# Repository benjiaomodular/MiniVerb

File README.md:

# MiniVerb
A reverb module based around the Daisy Seed platform.

## PCB Versions
### 2.1
Finally, a working SMT version

Download zip files from: [Hardware/MiniVerb v2.1/Fabrication](Hardware/MiniVerb%20v2.1/Fabrication)

### 2.0 (not working)
First SMT Release. This version was unusable.
- Added a single CV input

### 1.1
First batch of corrections
- Fixed pot connections
- Make IN(R) use IN(L) when no jack is inserted.

Download zip files from: [Hardware/MiniVerb v1.1/Fabrication](Hardware/MiniVerb%20v1.1/Fabrication)

### 1.0 (not working)
Initial release (does not work out of the box)
- Pots connected to the wrong pins on the Daisy

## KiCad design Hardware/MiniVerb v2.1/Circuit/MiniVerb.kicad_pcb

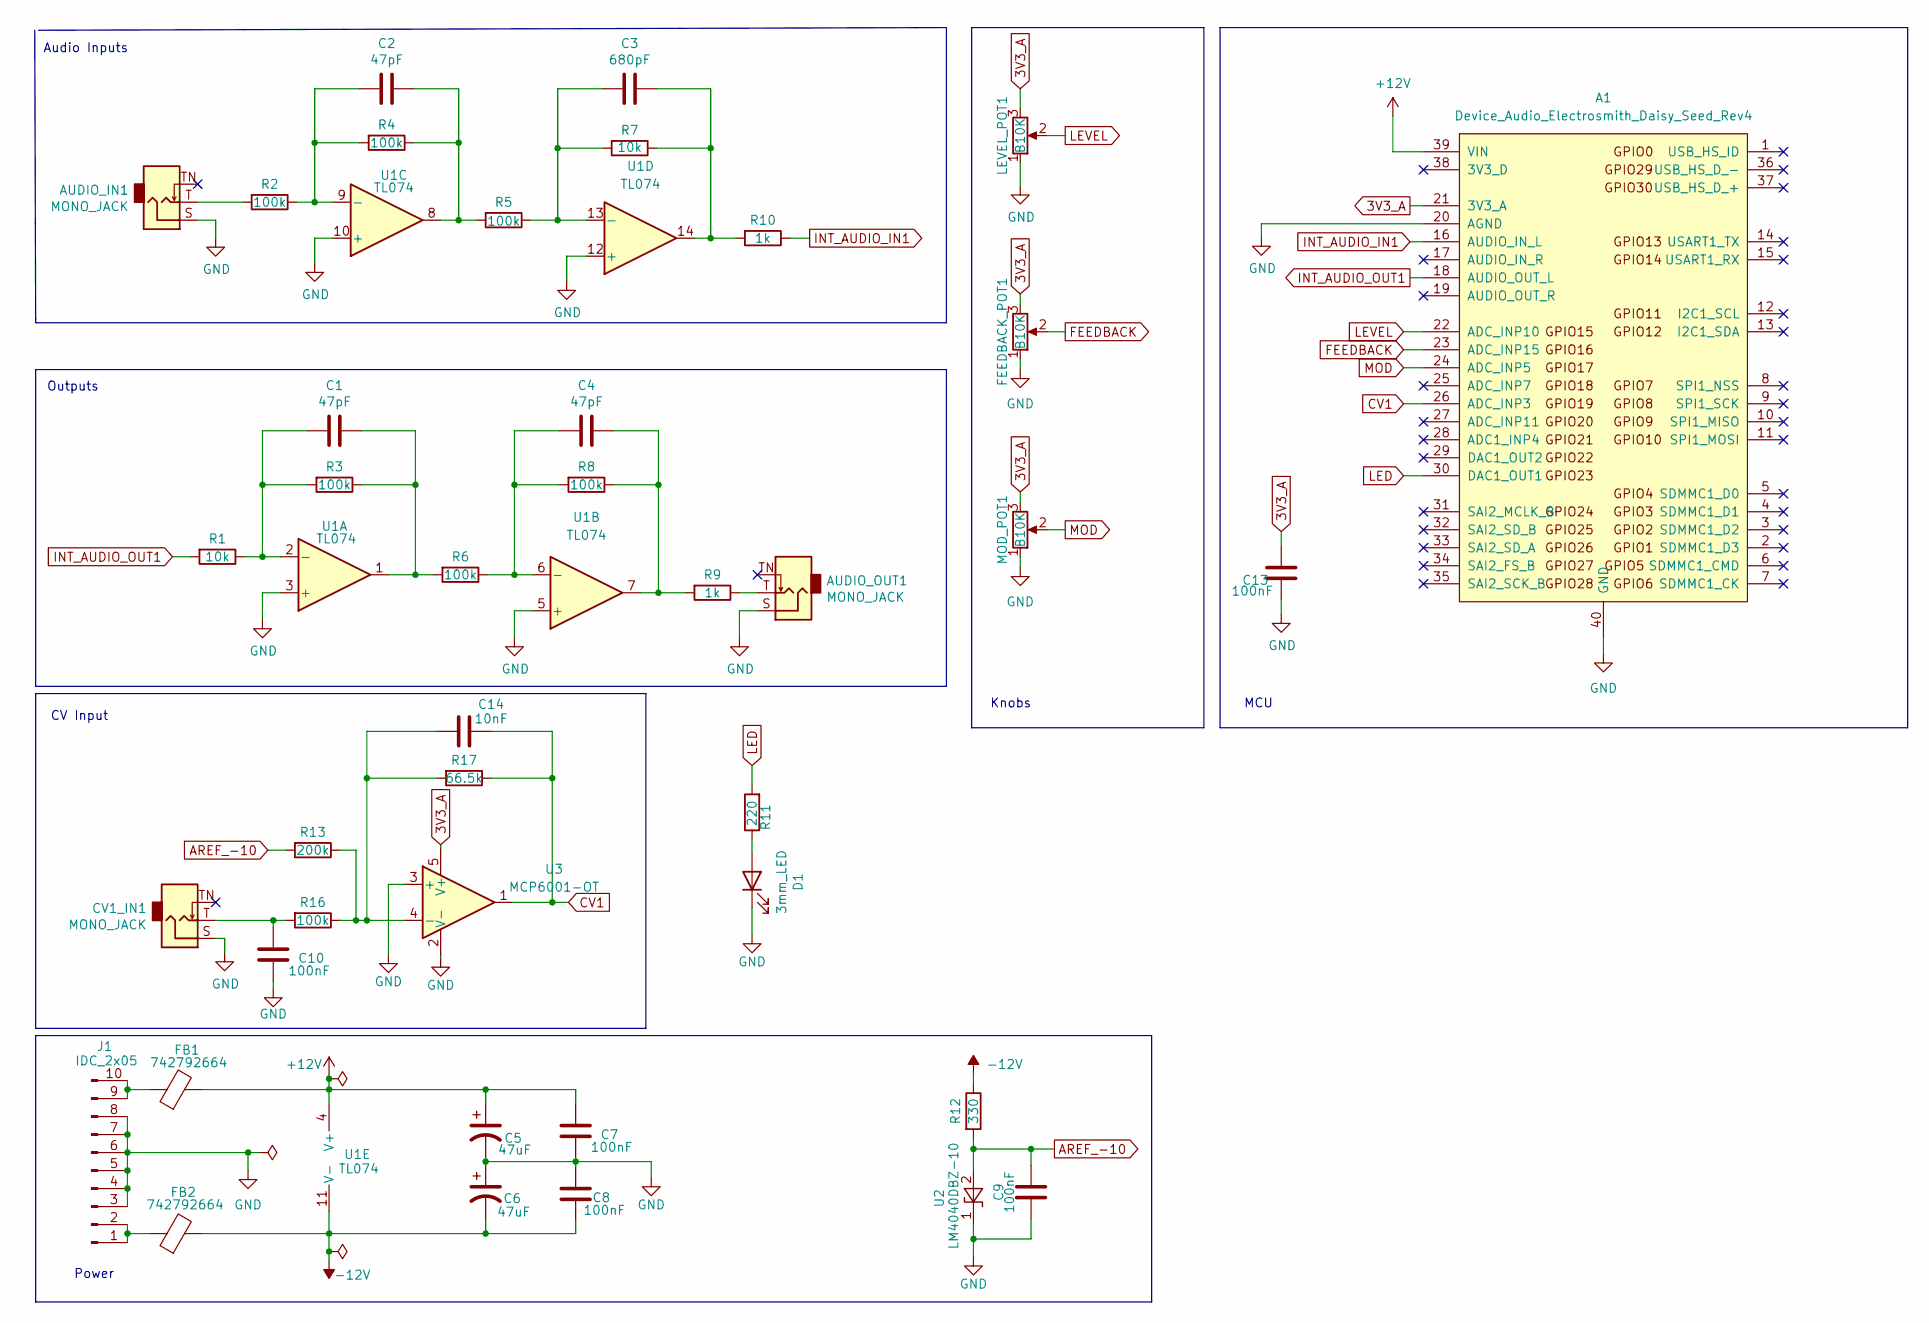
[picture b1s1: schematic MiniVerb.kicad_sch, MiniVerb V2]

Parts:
A1: Device_Audio_Electrosmith_Daisy_Seed_Rev4; Device_Audio_Electrosmith_Daisy_Seed
AUDIO_IN1: MONO_JACK; AudioJack_3.5mm; Manufacturers Part Numb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 PJ-3001F
AUDIO_OUT1: MONO_JACK; AudioJack_3.5mm; Manufacturers Part Numb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 PJ-3001F
C1, C2, C4: 47pF; C_0603_1608Metric_Pad1.08x0.95mm_HandSolder; Manufacturers Part Numb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 CC0603JRNPO9BN470
C3: 680pF; C_0603_1608Metric_Pad1.08x0.95mm_HandSolder; Manufacturers Part Numb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 VJ0603Y681KXAAC
C5, C6: 47uF; C_0805_2012Metric_Pad1.18x1.45mm_HandSolder; Manufacturers Part Numb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 GRM219R60J476ME44D
C7, C8, C9, C10, C13: 100nF; C_0603_1608Metric_Pad1.08x0.95mm_HandSolder; Manufacturers Part Numb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 CC0805KRX7R9BB104
C14: 10nF; C_0603_1608Metric_Pad1.08x0.95mm_HandSolder; Manufacturers Part Numb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 CC0603JRX7R9BB103
CV1_IN1: MONO_JACK; AudioJack_3.5mm; Manufacturers Part Numb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 PJ-3001F
D1: 3mm_LED; LED_D3.0mm; Manufacturers Part Numb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 EL304RD; LCSC Part # C2856645
FB1, FB2: 742792664; C_0603_1608Metric_Pad1.08x0.95mm_HandSolder; Manufacturers Part Numb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 742792664
FEEDBACK_POT1: B10K; Potentiometer_RV09_NoBracket; Manufacturers Part Numb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 RD901F-40-15R1-B10K
J1: IDC_2x05; IDC-Header_2x05_P2.54mm_Vertical; Manufacturers Part Numb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 X9555WV-2X05-6TV01; LCSC Part # C706914
LEVEL_POT1: B10K; Potentiometer_RV09_NoBracket; Manufacturers Part Numb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 RD901F-40-15R1-B10K
MOD_POT1: B10K; Potentiometer_RV09_NoBracket; Manufacturers Part Numb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 RD901F-40-15R1-B10K
R1, R7: 10k; R_0603_1608Metric_Pad0.98x0.95mm_HandSolder; Manufacturers Part Numb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 AC0603FR-0710KL
R2, R3, R4, R5, R6, R8, R16: 100k; R_0603_1608Metric_Pad0.98x0.95mm_HandSolder; Manufacturers Part Numb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 RC0603FR-07100KL
R9, R10: 1k; R_0603_1608Metric_Pad0.98x0.95mm_HandSolder; Manufacturers Part Numb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 RC0603FR-071KL
R11: 220; R_0603_1608Metric_Pad0.98x0.95mm_HandSolder; Mfg # AC0603FR-0710KL; LCSC Part # C116677
R12: 330; R_0603_1608Metric_Pad0.98x0.95mm_HandSolder; Manufacturers Part Numb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 CRG0603F330R
R13: 200k; R_0603_1608Metric_Pad0.98x0.95mm_HandSolder; Manufacturers Part Numb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 RC0603FR-07100KL
R17: 66.5k; R_0603_1608Metric_Pad0.98x0.95mm_HandSolder; Manufacturers Part Numb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 RC0603FR-0766K5L
U1: TL074; SOIC-14_3.9x8.7mm_P1.27mm; Manufacturers Part Numb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 TL074HIDYYR
U2: LM4040DBZ-10; SOT-23; Manufacturers Part Numb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 LM4040CIM3-10.0/NOPB
U3: MCP6001-OT; SOT-23-5; Manufacturers Part Numb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 MCP6001T-E/OT

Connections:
3V3_A: A1.21 (3V3_A), C13.1, FEEDBACK_POT1.3, LEVEL_POT1.3, MOD_POT1.3, U3.5 (V+)
+12V: A1.39 (VIN), C5.1, C7.1, FB1.2, U1.4 (V+)
-12V: C6.2, C8.2, FB2.2, R12.1, U1.11 (V-)
AREF_-10: C9.1, R12.2, R13.2, U2.2 (A)
CV1: A1.26 (ADC_INP3), C14.1, R17.1, U3.1
FEEDBACK: A1.23 (ADC_INP15), FEEDBACK_POT1.2
GND: A1.20 (AGND), A1.40 (GND), AUDIO_IN1.S, AUDIO_OUT1.S, C5.2, C6.1, C7.2, C8.1, C9.2, C10.2, C13.2, CV1_IN1.S, D1.1 (K), FEEDBACK_POT1.1, J1.3, J1.4, J1.5, J1.6, J1.7, J1.8, LEVEL_POT1.1, MOD_POT1.1, U1.3 (+), U1.5 (+), U1.10 (+), U1.12 (+), U2.1 (K), U3.2 (V-), U3.3 (+)
INT_AUDIO_IN1: A1.16 (AUDIO_IN_L), R10.1
INT_AUDIO_OUT1: A1.18 (AUDIO_OUT_L), R1.2
LED: A1.30 (DAC1_OUT1), R11.2
LEVEL: A1.22 (ADC_INP10), LEVEL_POT1.2
MOD: A1.24 (ADC_INP5), MOD_POT1.2
unnamed: AUDIO_IN1.T, R2.2
unnamed: AUDIO_OUT1.T, R9.1
unnamed: C1.1, R3.1, R6.2, U1.1
unnamed: C1.2, R1.1, R3.2, U1.2 (-)
unnamed: C2.1, R4.1, R5.2, U1.8
unnamed: C2.2, R2.1, R4.2, U1.9 (-)
unnamed: C3.1, R7.1, R10.2, U1.14
unnamed: C3.2, R5.1, R7.2, U1.13 (-)
unnamed: C4.1, R8.1, R9.2, U1.7
unnamed: C4.2, R6.1, R8.2, U1.6 (-)
unnamed: C10.1, CV1_IN1.T, R16.2
unnamed: C14.2, R13.1, R16.1, R17.2, U3.4 (-)
unnamed: D1.2 (A), R11.1
unnamed: FB1.1, J1.9, J1.10
unnamed: FB2.1, J1.1, J1.2

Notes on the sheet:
CV Input
Power
Outputs
Knobs
MCU
Audio Inputs

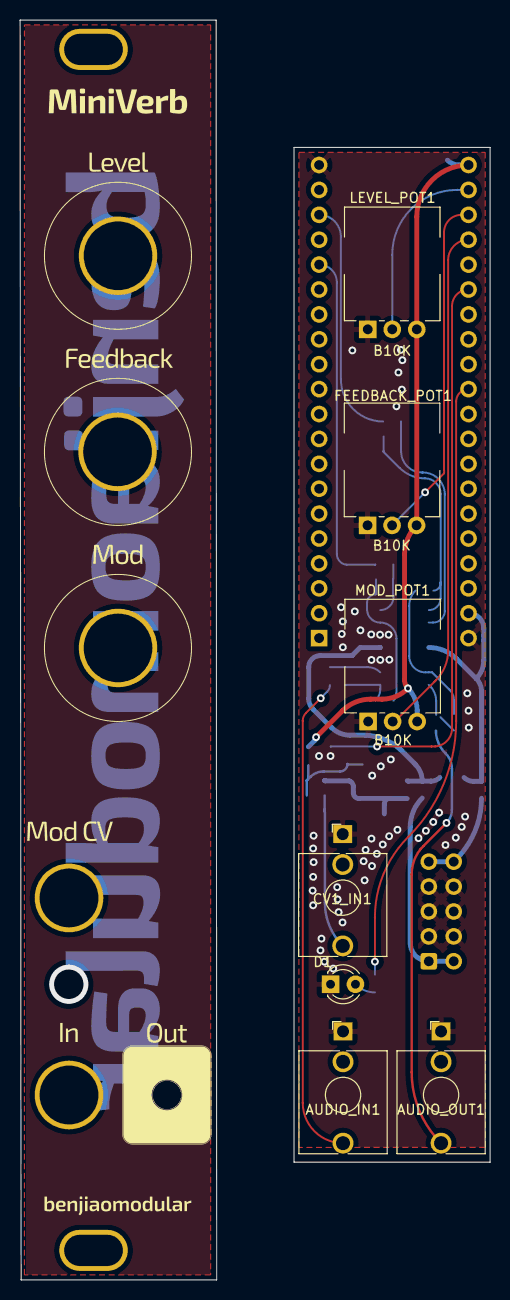
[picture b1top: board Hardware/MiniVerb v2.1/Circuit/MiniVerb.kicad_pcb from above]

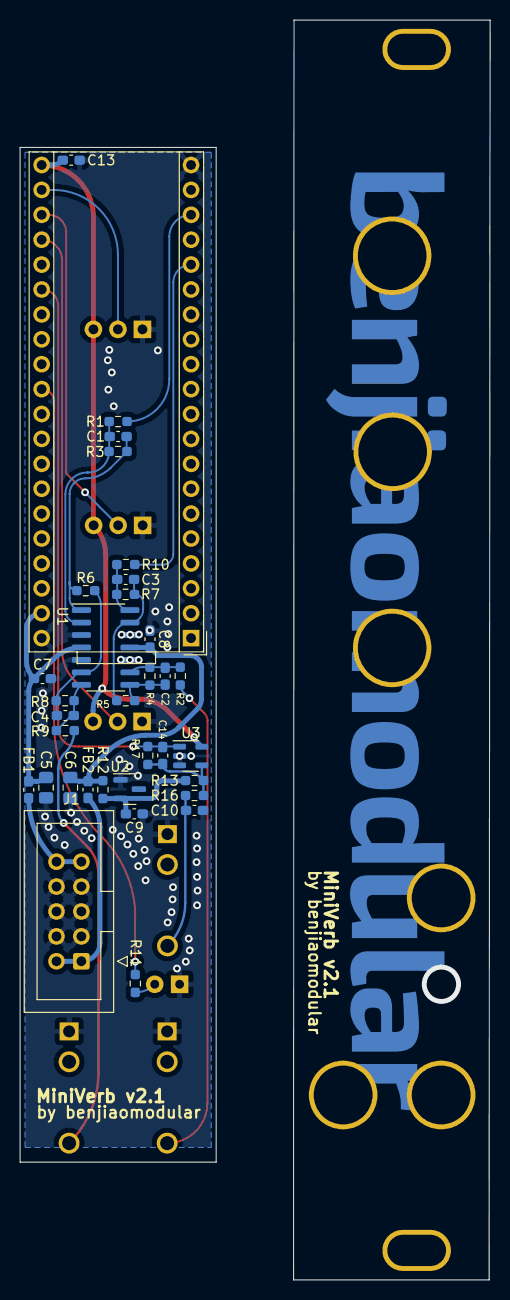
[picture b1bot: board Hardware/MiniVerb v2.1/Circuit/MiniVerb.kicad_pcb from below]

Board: 2 copper layers, 20.0 x 103.5 mm, 41 parts (34 on the bottom side), 27 nets.

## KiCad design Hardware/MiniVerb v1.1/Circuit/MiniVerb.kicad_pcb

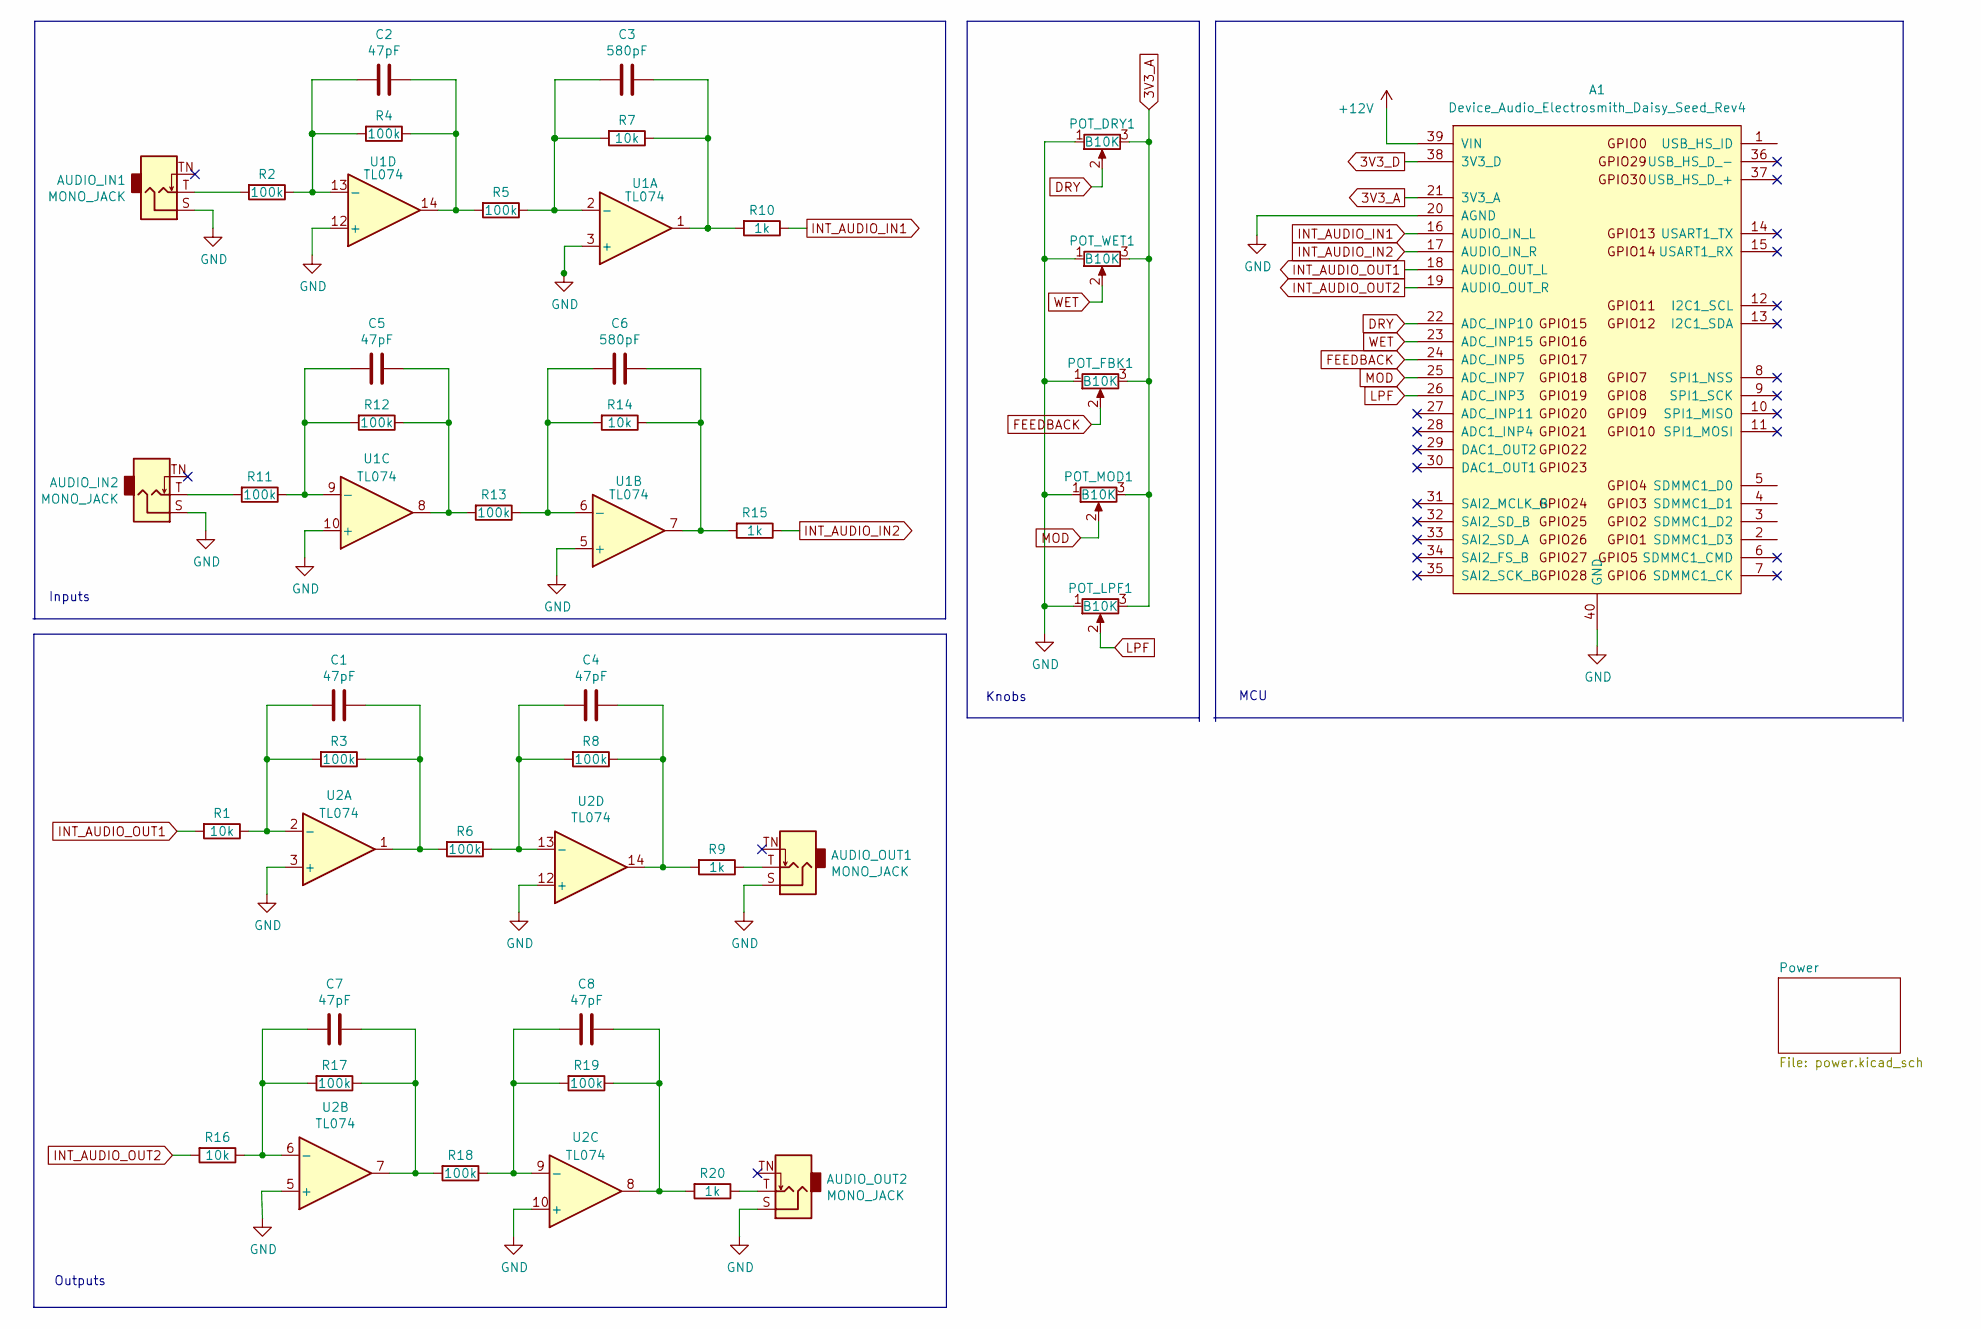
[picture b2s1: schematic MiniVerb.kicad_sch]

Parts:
A1: Device_Audio_Electrosmith_Daisy_Seed_Rev4; Device_Audio_Electrosmith_Daisy_Seed
AUDIO_IN1, AUDIO_IN2: MONO_JACK; AudioJack_3.5mm
AUDIO_OUT1, AUDIO_OUT2: MONO_JACK; AudioJack_3.5mm
C1, C2, C4, C5, C7, C8: 47pF; Capacitor_Disc_D3.8mm_W2.6mm_P2.50mm
C3, C6: 580pF; Capacitor_Rect_L7.2mm_W2.5mm_P5.00mm
POT_DRY1: B10K; Potentiometer_RV09
POT_FBK1: B10K; Potentiometer_RV09
POT_LPF1: B10K; Potentiometer_RV09
POT_MOD1: B10K; Potentiometer_RV09
POT_WET1: B10K; Potentiometer_RV09
R1, R7, R14, R16: 10k; Resistor_L6.3mm_D2.5mm_P7.62mm_Horizontal
R2, R3, R4, R5, R6, R8, R11, R12, R13, R17, R18, R19: 100k; Resistor_L6.3mm_D2.5mm_P7.62mm_Horizontal
R9, R10, R15, R20: 1k; Resistor_L6.3mm_D2.5mm_P7.62mm_Horizontal
U1, U2: TL074; DIP-14_W7.62mm

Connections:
3V3_A: A1.21 (3V3_A), POT_DRY1.3, POT_FBK1.3, POT_LPF1.3, POT_MOD1.3, POT_WET1.3
3V3_D: A1.38 (3V3_D)
+12V: A1.39 (VIN); also elsewhere on the board
DRY: A1.22 (ADC_INP10), POT_DRY1.2
FEEDBACK: A1.24 (ADC_INP5), POT_FBK1.2
GND: A1.20 (AGND), A1.40 (GND), AUDIO_IN1.S, AUDIO_IN2.S, AUDIO_OUT1.S, AUDIO_OUT2.S, POT_DRY1.1, POT_FBK1.1, POT_LPF1.1, POT_MOD1.1, POT_WET1.1, U1.3 (+), U1.5 (+), U1.10 (+), U1.12 (+), U2.3 (+), U2.5 (+), U2.10 (+), U2.12 (+); also elsewhere on the board
INT_AUDIO_IN1: A1.16 (AUDIO_IN_L), R10.1
INT_AUDIO_IN2: A1.17 (AUDIO_IN_R), R15.1
INT_AUDIO_OUT1: A1.18 (AUDIO_OUT_L), R1.2
INT_AUDIO_OUT2: A1.19 (AUDIO_OUT_R), R16.2
LPF: A1.26 (ADC_INP3), POT_LPF1.2
MOD: A1.25 (ADC_INP7), POT_MOD1.2
unnamed: AUDIO_IN1.T, R2.2
unnamed: AUDIO_IN2.T, R11.2
unnamed: AUDIO_OUT1.T, R9.1
unnamed: AUDIO_OUT2.T, R20.1
unnamed: C1.1, R3.1, R6.2, U2.1
unnamed: C1.2, R1.1, R3.2, U2.2 (-)
unnamed: C2.1, R4.1, R5.2, U1.14
unnamed: C2.2, R2.1, R4.2, U1.13 (-)
unnamed: C3.1, R7.1, R10.2, U1.1
unnamed: C3.2, R5.1, R7.2, U1.2 (-)
unnamed: C4.1, R8.1, R9.2, U2.14
unnamed: C4.2, R6.1, R8.2, U2.13 (-)
unnamed: C5.1, R12.1, R13.2, U1.8
unnamed: C5.2, R11.1, R12.2, U1.9 (-)
unnamed: C6.1, R14.1, R15.2, U1.7
unnamed: C6.2, R13.1, R14.2, U1.6 (-)
unnamed: C7.1, R17.1, R18.2, U2.7
unnamed: C7.2, R16.1, R17.2, U2.6 (-)
unnamed: C8.1, R19.1, R20.2, U2.8
unnamed: C8.2, R18.1, R19.2, U2.9 (-)
WET: A1.23 (ADC_INP15), POT_WET1.2

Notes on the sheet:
Inputs
Outputs
Knobs
MCU

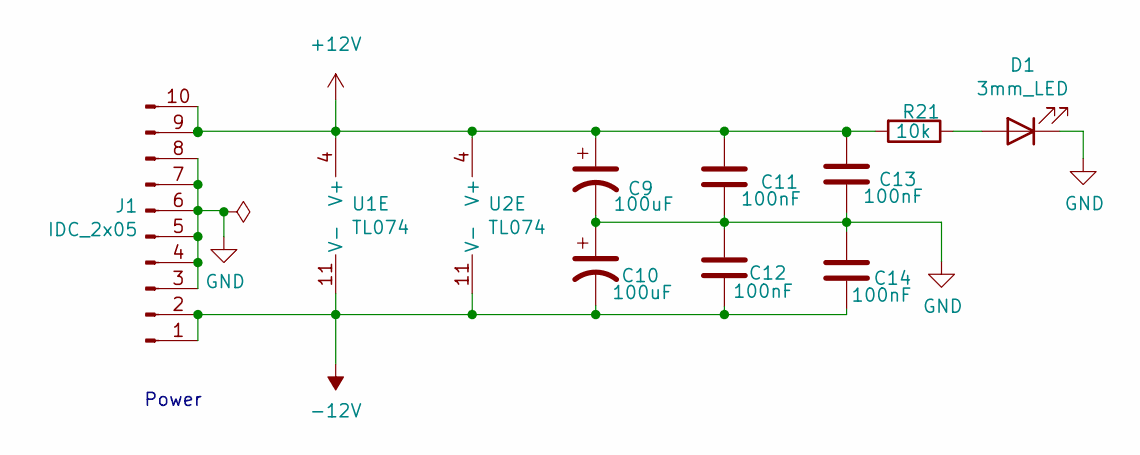
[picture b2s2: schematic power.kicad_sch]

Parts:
C9, C10: 100uF; Capacitor_Radial_D5.0mm_P2.5mm
C11, C12, C13, C14: 100nF; Capacitor_Rect_L7.2mm_W2.5mm_P5.00mm
D1: 3mm_LED; LED_D3.0mm; Manufacturers Part Numb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 EL304RD; LCSC Part # C2856645
J1: IDC_2x05; IDC-Header_2x05_P2.54mm_Vertical; Manufacturers Part Numb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 X9555WV-2X05-6TV01; LCSC Part # C706914
R21: 10k; Resistor_L6.3mm_D2.5mm_P7.62mm_Horizontal; Mfg # AC0603FR-0710KL; LCSC Part # C116677
U1, U2: TL074; DIP-14_W7.62mm

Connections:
+12V: C9.1, C11.1, C13.1, J1.9, J1.10, R21.2, U1.4 (V+), U2.4 (V+); also elsewhere on the board
-12V: C10.2, C12.2, C14.2, J1.1, J1.2, U1.11 (V-), U2.11 (V-)
GND: C9.2, C10.1, C11.2, C12.1, C13.2, C14.1, D1.1 (K), J1.3, J1.4, J1.5, J1.6, J1.7, J1.8; also elsewhere on the board
unnamed: D1.2 (A), R21.1

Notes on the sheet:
Power

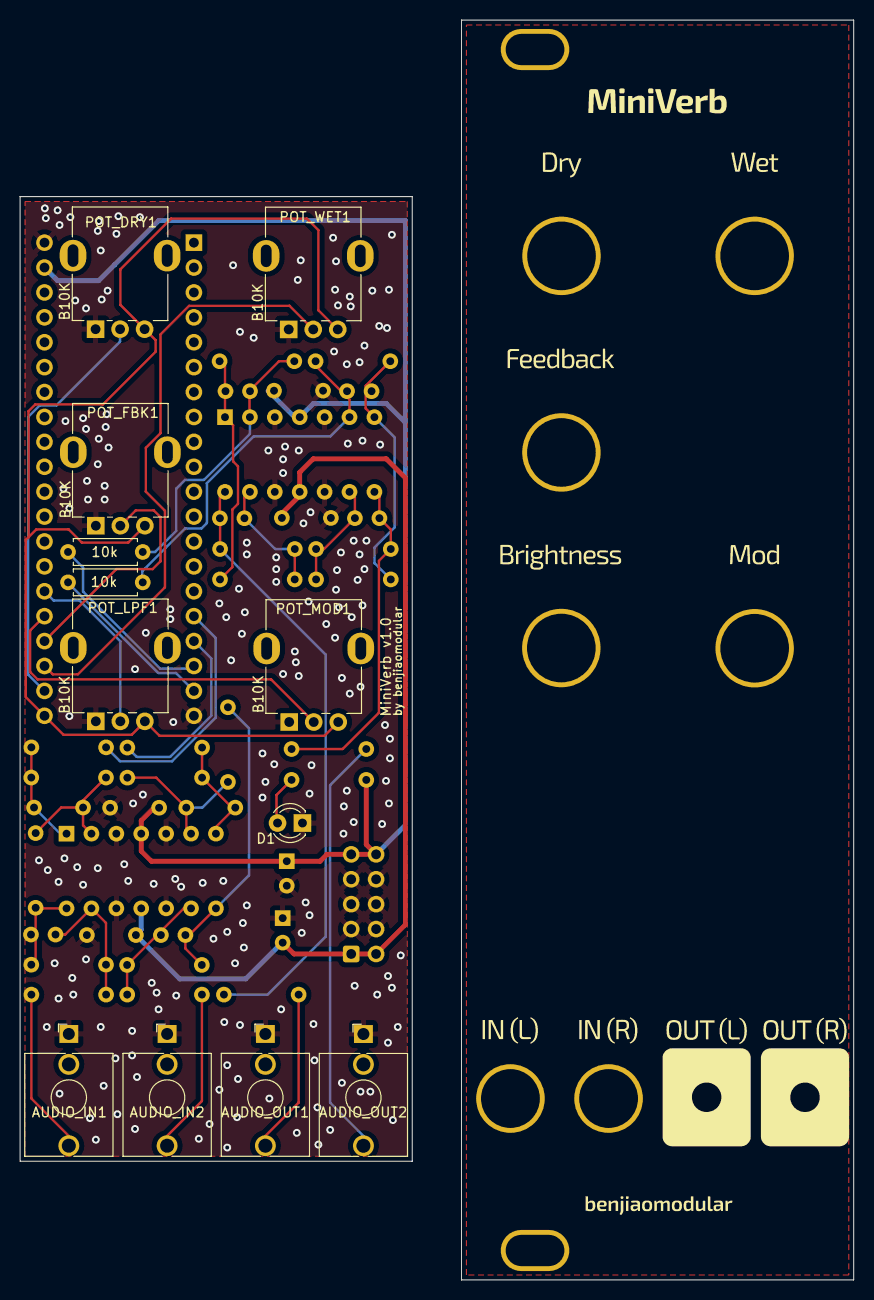
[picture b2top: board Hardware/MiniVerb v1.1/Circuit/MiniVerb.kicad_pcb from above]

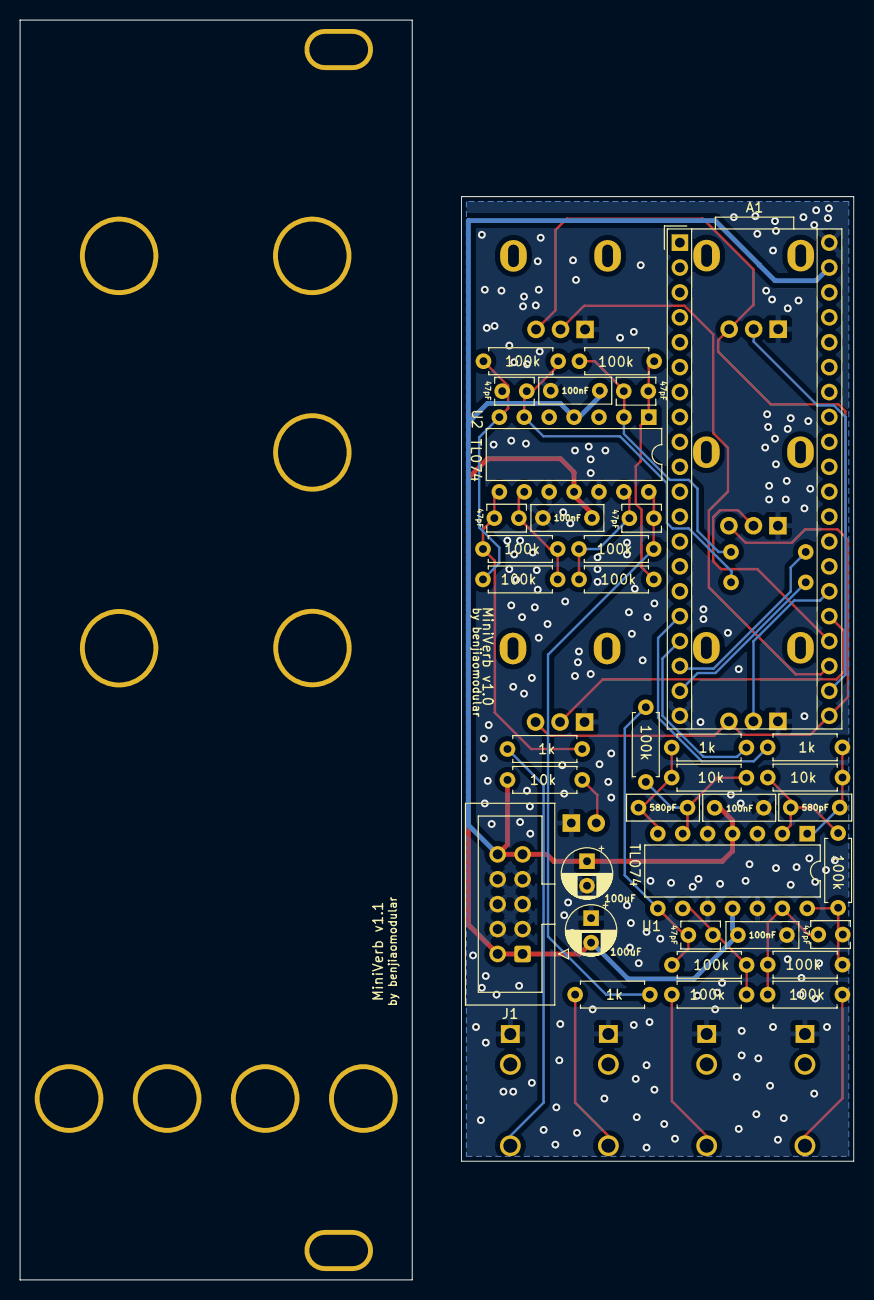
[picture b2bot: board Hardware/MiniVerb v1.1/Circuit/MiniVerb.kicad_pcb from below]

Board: 2 copper layers, 40.0 x 98.4 mm, 49 parts (37 on the bottom side), 34 nets.

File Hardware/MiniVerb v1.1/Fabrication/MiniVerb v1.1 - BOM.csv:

Reference, Quantity, Value, Manufacturers Name, Mfg #, Part Description
A1 ,1,Daisy Seed,Electro-Smith,,
AUDIO_IN1 AUDIO_OUT1 AUDIO_IN2 AUDIO_OUT2 ,4,Audio Jack,Tayda Electronics,PJ-3001F,
C1 C2 C4 C5 C7 C8 ,6,47pF,,,
C11 C12 C13 C14 ,4,100nF,,,
C3 C6 ,2,580pF,,,
C9 C10 ,2,100uF,,,
D1 ,1,3mm_LED,,,
J1 ,1,IDC_2x05,XKB Connectivity ,X9555WV-2X05-6TV01,IDC Connector 2x05 2.54mm Pitch Straight
POT_DRY1 POT_FBK1 POT_LPF1 POT_MOD1 POT_WET1 ,5,B10K,Alpha (Taiwan),RD901F-40-15R1-B10K,10K OHM Linear Taper Potentiometer Round Shaft PCB 9mm
R1 R7 R14 R16 R21 ,5,10k,,,
R2 R3 R4 R5 R6 R8 R11 R12 R13 R17 R18 R19 ,12,100k,,,
R9 R10 R15 R20 ,4,1k,,,
U1 U2 ,2,TL074,,,

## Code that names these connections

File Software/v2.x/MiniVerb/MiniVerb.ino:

// For benjiaomodular MiniVerb v2.x
// Based on reverbsc by Stephen Hensley

#include "DaisyDuino.h"

DaisyHardware hw;

size_t num_channels;
float sample_rate;

ReverbSc DSY_SDRAM_BSS verb;
static Jitter jitter;

float level, feedback, mod, cv1, jitterMixKnob;

float CtrlVal(uint8_t pin) {
  analogReadResolution(16);
  return (analogRead(pin)) / 65535.f;
}

void MyCallback(float **in, float **out, size_t size) {
  float dryIn, verbOut;
  float jitter_out;

  for (size_t i = 0; i < size; i++) {
    dryIn = in[0][i];
    jitter_out = jitter.Process();
    
    verb.Process(dryIn, 0, &verbOut, 0);
    out[0][i] = dryIn + verbOut * ((1 - cv1) + (jitter_out * cv1)) * level;

  }
}

void setup() {

  // Initialize for Daisy pod at 48kHz
  hw = DAISY.init(DAISY_SEED, AUDIO_SR_48K);
  num_channels = hw.num_channels;
  sample_rate = DAISY.get_samplerate();

  // Initialize reverb
  verb.Init(sample_rate);
  verb.SetFeedback(0.95f);
  verb.SetLpFreq(18000.0f);

  jitter.Init(sample_rate);
  jitter.SetAmp(1);
  jitter.SetCpsMin(1);
  jitter.SetCpsMax(25);

  level = 0.1f;
  DAISY.begin(MyCallback);
}

void loop() {
  level = CtrlVal(A0); // pin 22
  feedback = CtrlVal(A1); // pin 23
  mod = CtrlVal(A2); // pin 24
  cv1 = 1-CtrlVal(A4); // pin 26
 
  verb.SetFeedback(0.8 + 0.2 * feedback);
  verb.SetLpFreq(mod * 20000.0f);
}

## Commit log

2022-12-14 initial panel
2023-01-21 Fixed mistakes from v1.0
2023-01-24 Use TN pin for IN (R)
2023-02-02 Added SMT version
2023-02-02 Added gerber files for v1.1 front panel
2023-02-02 Fixed stereo reverb output
2023-02-10 Added BOM
2023-02-10 Added schematics
2023-02-10 cleanup
2023-02-10 Added link to gerber files
2023-02-17 Updated BOM
2023-02-17 Updated bom zip
2023-02-17 Added pin headers
2023-02-28 Added initial code for v2
2023-02-28 Commit pdf for v2
2023-03-01 Updated front panel :
2023-03-22 working software and hardware for v2.1
2023-04-26 cleanup and ibom
2023-05-09 Added v2.1 to docs
2023-08-12 Marked broken gerbers
2023-08-24 Update MiniVerb.ino
    Add missing slashes for comment
